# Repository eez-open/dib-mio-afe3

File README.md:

### Ownership and License
The contributors are listed in CONTRIB.TXT.

Licenses | OSHWA UID
--|--
 | 

### Overview

The [EEZ DIB](https://github.com/eez-open/modular-psu) 4-channel Hi-voltage/Hi-current AFE for [MIO168](https://github.com/eez-open/dib-mio168) module with two isolated inputs for voltage and current measurements.

### Feature list
* [ADS131E04](https://www.ti.com/product/ADS131E04) 24-bit 4-channel simultaneous sampling ADC with SPI
* AIN#1: Hi-voltage isolated (floated) input featuring 2 measurement ranges (±50 V, ±450 V)
* AIN#2: Hi-current isolated (floated) input featuring 2 measurement ranges (±1 A, ±10 A)
* AIN#3: Hi-voltage input featuring 3 measurement ranges (±2.4 V, ±48 V, ±240 V)
* AIN#4: Hi-current input featuring 3 measurement ranges (±24 mA, ±1.2 A, ±10 A), share common GND with AIN#3
* Latching relays for lower continuous power consumption
* Fused current inputs
* On-board ±2.5 V low noise LDOs
* Optional external voltage reference
* Dimensions: 132 x 68.5 mm, 4-layer PCB

### r1B4 prototype 3D model

### KiCad project (v7 or newer)

* [AFE3 r1B4](https://github.com/eez-open/dib-mio-afe3/tree/master/EDA%20files/KiCad)

All symbols, footprints and 3D models used in the project can be found in the [EEZ-DIB Library](https://github.com/eez-open/eez-kicad-libraries) plugin for KiCad.

### Bill of materials

* [Download](https://github.com/eez-open/dib-mio-afe3/tree/master/EDA%20files/KiCad/bom/ibom.html) as raw file _Interactive BOM_ (ibom.html) and open it locally in your browser.

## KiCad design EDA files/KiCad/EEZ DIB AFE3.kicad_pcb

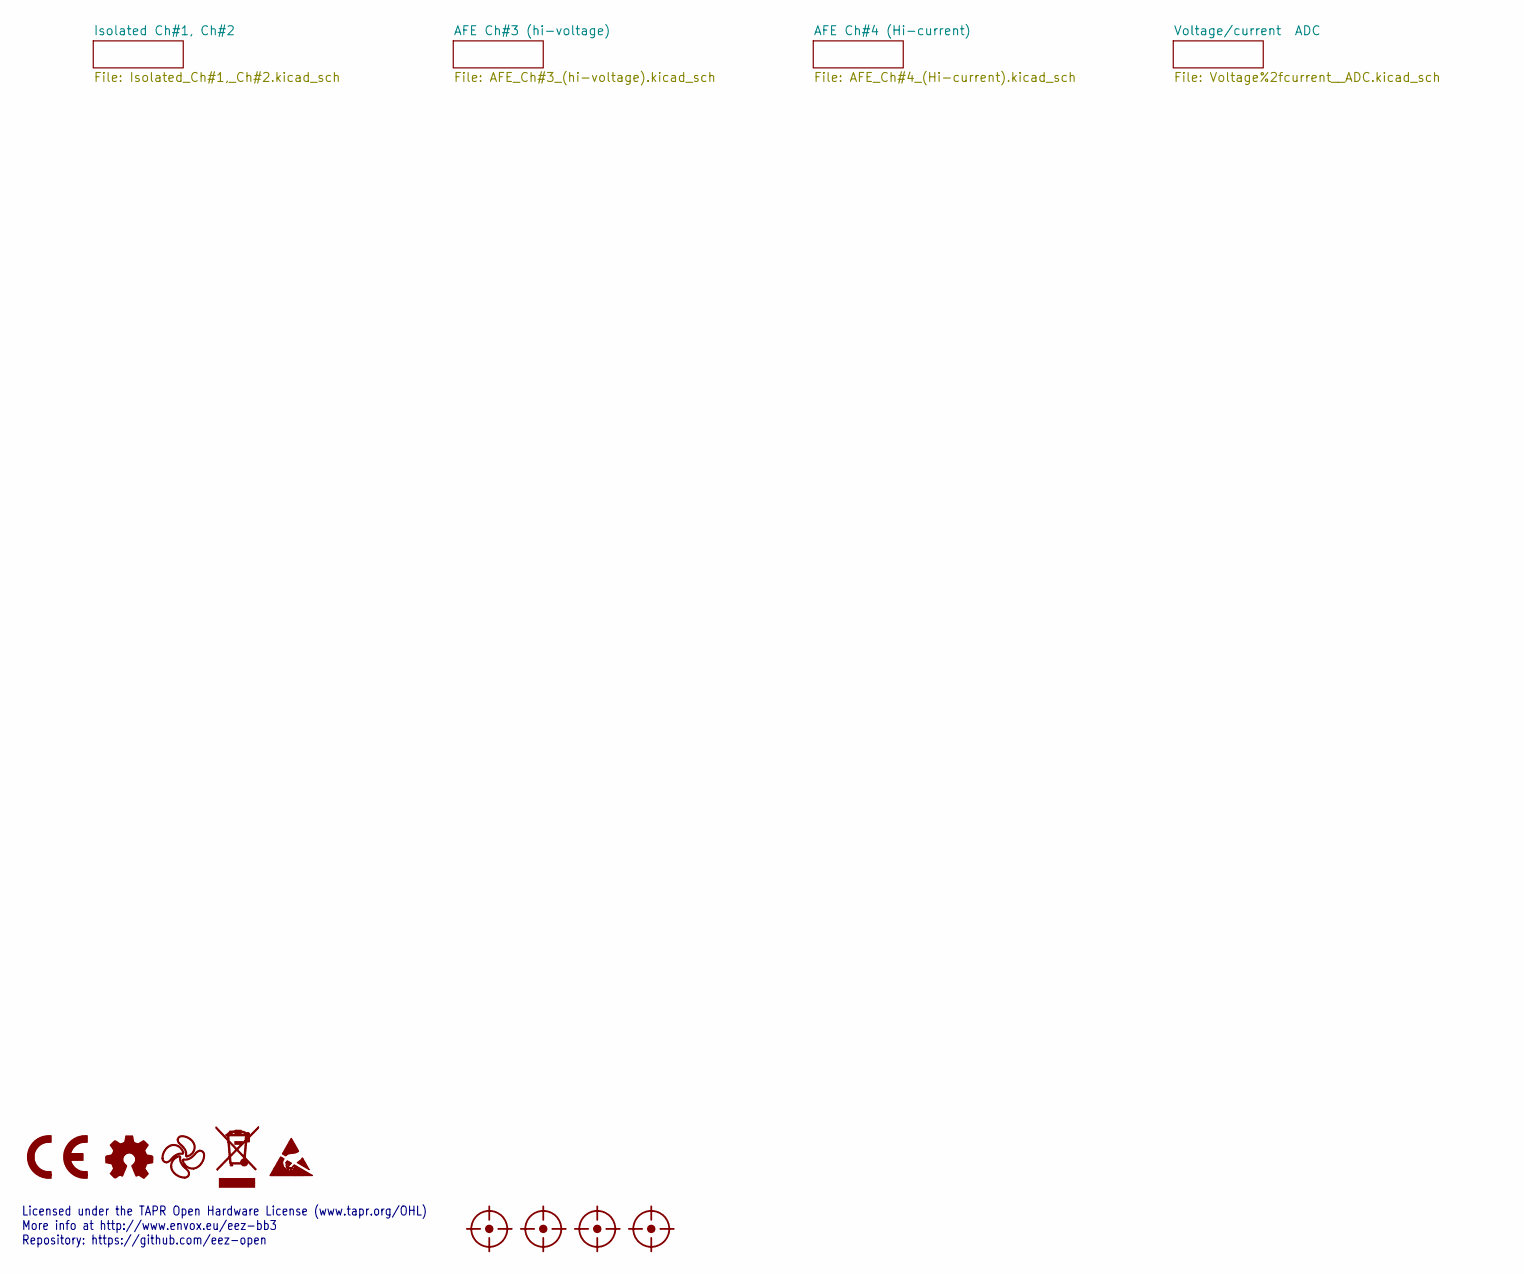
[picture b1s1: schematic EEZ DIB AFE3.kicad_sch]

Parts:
FM1, FM2, FM3, FM4: FIDUCIAL_2; Fiducial
LOGO1: CR logo; CE logo
LOGO2: Open HW logo
LOGO3: EEZ logo; EEZ logo (outline 6mm)
LOGO4: WEEE logo
LOGO5: ESD logo

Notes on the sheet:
Licensed under the TAPR Open Hardware License (www.tapr.org/OHL) More info at http://www.envox.eu/eez-bb3 Repository: https://github.com/eez-open

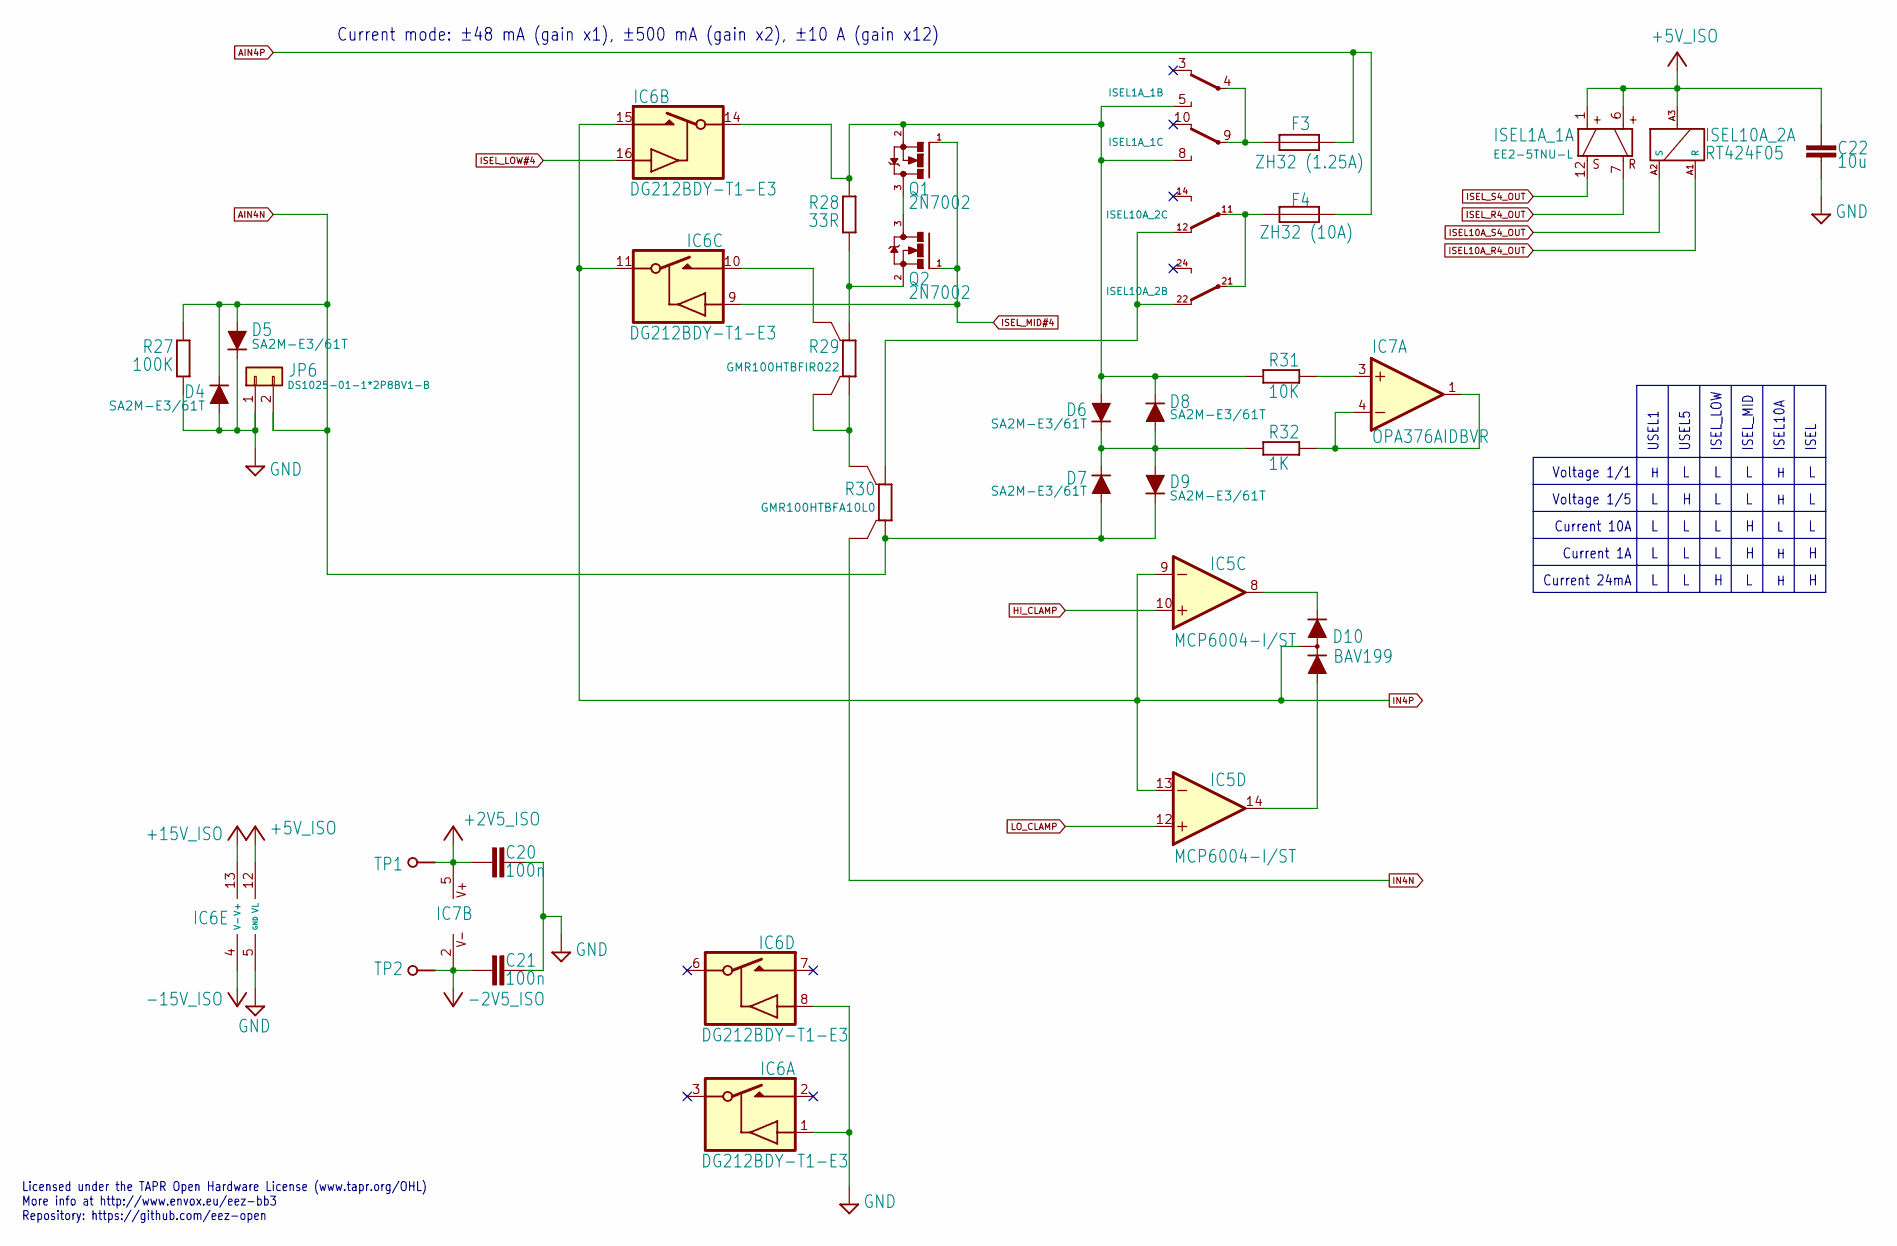
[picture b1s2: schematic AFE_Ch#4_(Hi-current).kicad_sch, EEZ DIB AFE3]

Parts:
C20, C21: 100n; C_0603_1608Metric; DigiKey 490-4774-1-ND
C22: 10u; C_1206_3216Metric; DigiKey 1276-2872-1-ND
D4, D5, D6, D7, D8, D9: SA2M-E3/61T; DO214AC-2; DigiKey CSA2M-E3/IGICT-ND
D10: BAV199; SOT23-3; DigiKey 1727-6382-1-ND
F3: ZH32 (1.25A); ZH32; DigiKey 732-11370-ND
F4: ZH32 (10A); ZH32; DigiKey 732-11370-ND
IC5: MCP6004-I/ST; PW(R-PDSO-G14); DigiKey MCP6004T-I/STTR-ND
IC6: DG212BDY-T1-E3; SO16; DigiKey DG212BDY-T1-E3CT-ND
IC7: OPA376AIDBVR; SOT23-5L_STM; DigiKey 296-39130-2-ND
ISEL1A_1: EE2-5TNU-L; DigiKey 399-11021-1-ND
ISEL10A_2: RT424F05; DigiKey PB2024-ND
JP6: DS1025-01-1*2P8BV1-B; 2MM-2; DigiKey 2057-2PH1-02-UA-ND
Q1, Q2: 2N7002; SOT103P240X110-3N; DigiKey 2N7002LT1GOSCT-ND
R27: 100K; R_1206_3216Metric; DigiKey RMCF0805FT100KCT-ND
R28: 33R; R_1206_3216Metric; DigiKey 13-RT1206BRD0733RLCT-ND
R29: GMR100HTBFIR022; R_2512-4WIRE; DigiKey 511-1688-1-ND
R30: GMR100HTBFA10L0; R_2512-4WIRE; DigiKey 511-1686-1-ND
R31: 10K; R_0805_2012Metric; DigiKey 311-10.0KCRCT-ND
R32: 1K; R_0805_2012Metric; DigiKey RC0805FR-071KL
TP1, TP2: PCB_TEST_TABSHIELD; Testhole 24_50mils

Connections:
+2V5_ISO: C20.2, IC7.5 (V+), TP1.1; also elsewhere on the board
+5V_ISO: C22.1, IC6.12 (VL), ISEL1A_1.1 (S+), ISEL1A_1.6 (R+), ISEL10A_2.A3; also elsewhere on the board
+15V_ISO: IC6.13 (V+); also elsewhere on the board
-2V5_ISO: C21.2, IC7.2 (V-), TP2.1; also elsewhere on the board
-15V_ISO: IC6.4 (V-); also elsewhere on the board
AIN4N: D4.C, D5.A, D7.A, D9.C, JP6.2, R27.2, R30.1; also elsewhere on the board
AIN4P: F3.2, F4.2; also elsewhere on the board
GND: C20.1, C21.1, C22.2, D4.A, D5.C, IC6.1 (IN), IC6.5 (GND), IC6.8 (IN), JP6.1, R27.1; also elsewhere on the board
HI_CLAMP: IC5.10 (+IN); also elsewhere on the board
IN4N: R30.1S; also elsewhere on the board
IN4P: D10.3 (AC), IC5.9 (-IN), IC5.13 (-IN), IC6.11 (S), IC6.15 (D); also elsewhere on the board
ISEL10A_R4_OUT: ISEL10A_2.A1 (R); also elsewhere on the board
ISEL10A_S4_OUT: ISEL10A_2.A2 (S); also elsewhere on the board
ISEL_LOW#4: IC6.16 (IN); also elsewhere on the board
ISEL_MID#4: IC6.9 (IN), Q1.1 (G), Q2.1 (G); also elsewhere on the board
ISEL_R4_OUT: ISEL1A_1.7 (R-); also elsewhere on the board
ISEL_S4_OUT: ISEL1A_1.12 (S-); also elsewhere on the board
LO_CLAMP: IC5.12 (+IN); also elsewhere on the board
unnamed: D6.C, D7.C, D8.A, D9.A, R32.2
unnamed: D10.1 (A), IC5.14 (OUT)
unnamed: D10.2 (C), IC5.8 (OUT)
unnamed: F4.1, ISEL10A_2.11, ISEL10A_2.21
unnamed: D6.A, D8.C, IC6.14 (S), ISEL1A_1.5 (NO), ISEL1A_1.8 (NO), Q1.2 (S), R28.2, R31.2
unnamed: IC6.10 (D), R29.2S
unnamed: IC7.3 (+IN), R31.1
unnamed: IC7.1 (OUT), IC7.4 (-IN), R32.1
unnamed: F3.1, ISEL1A_1.4 (COM), ISEL1A_1.9 (COM)
unnamed: ISEL10A_2.12, ISEL10A_2.22, R30.2
unnamed: Q1.3 (D), Q2.3 (D)
unnamed: Q2.2 (S), R28.1, R29.2
unnamed: R29.1, R29.1S, R30.2S

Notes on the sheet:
Current 24mA
Voltage 1/1
USEL5
Current 10A
Current mode: ±48 mA (gain x1), ±500 mA (gain x2), ±10 A (gain x12)
ISEL_LOW
ISEL
USEL1
ISEL_MID
Current 1A
Voltage 1/5
Licensed under the TAPR Open Hardware License (www.tapr.org/OHL) More info at http://www.envox.eu/eez-bb3 Repository: https://github.com/eez-open
ISEL10A

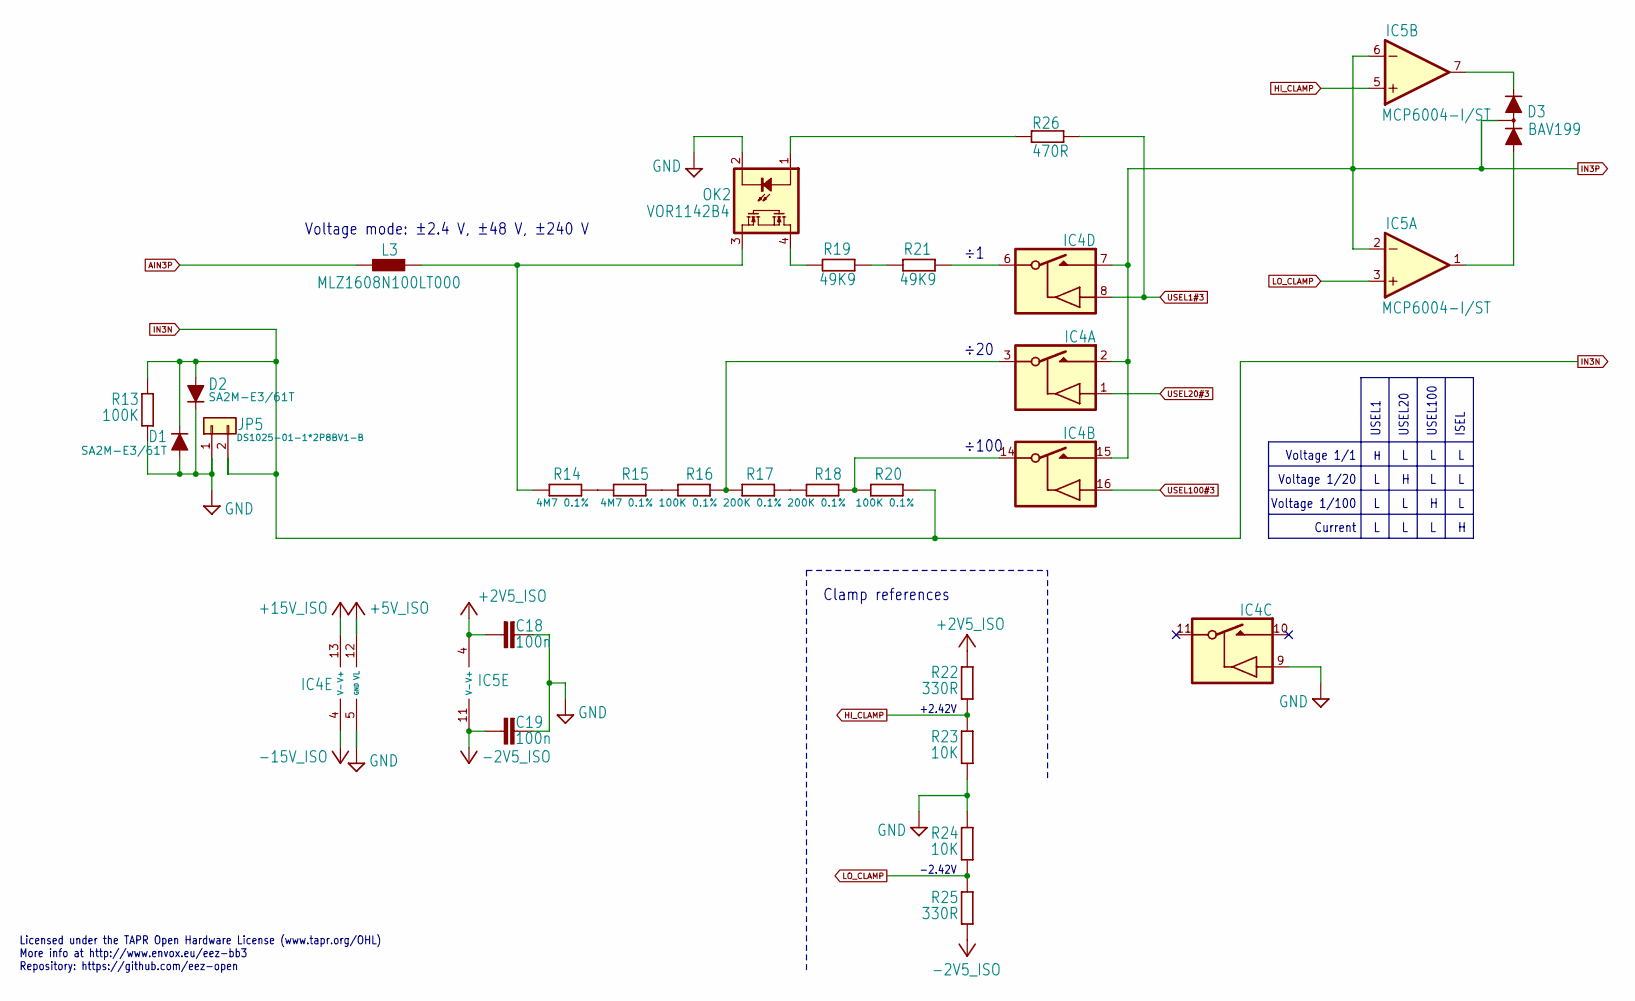
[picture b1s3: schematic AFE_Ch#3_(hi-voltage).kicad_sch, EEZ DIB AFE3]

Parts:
C18, C19: 100n; C_0603_1608Metric; DigiKey 490-4774-1-ND
D1, D2: SA2M-E3/61T; DO214AC-2; DigiKey CSA2M-E3/IGICT-ND
D3: BAV199; SOT23-3; DigiKey 1727-6382-1-ND
IC4: DG212BDY-T1-E3; SO16; DigiKey DG212BDY-T1-E3CT-ND
IC5: MCP6004-I/ST; PW(R-PDSO-G14); DigiKey MCP6004T-I/STTR-ND
JP5: DS1025-01-1*2P8BV1-B; 2MM-2; DigiKey 2057-2PH1-02-UA-ND
L3: MLZ1608N100LT000; BEAD0603; DigiKey 445-6755-1-ND
OK2: VOR1142B4; DIL4-SMD; DigiKey VOR1142B4-ND
R13: 100K; R_1206_3216Metric; DigiKey RMCF0805FT100KCT-ND
R14, R15: 4M7 0.1%; R_1206_3216Metric; DigiKey 408-2037-1-ND
R16, R20: 100K 0.1%; R_1206_3216Metric; DigiKey RG32P100KBCT-ND
R17, R18: 200K 0.1%; R_1206_3216Metric; DigiKey RG32P200KBCT-ND
R19, R21: 49K9; R_1206_3216Metric; DigiKey RNCP1206FTD49K9CT-ND
R22, R25: 330R; R_0805_2012Metric; DigiKey A106061CT-ND
R23, R24: 10K; R_0805_2012Metric; DigiKey 311-10.0KCRCT-ND
R26: 470R; R_0805_2012Metric; DigiKey 311-470CRCT-ND

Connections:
+2V5_ISO: C18.2, IC5.4 (V+), R22.1; also elsewhere on the board
+5V_ISO: IC4.12 (VL); also elsewhere on the board
+15V_ISO: IC4.13 (V+); also elsewhere on the board
-2V5_ISO: C19.2, IC5.11 (V-), R25.2; also elsewhere on the board
-15V_ISO: IC4.4 (V-); also elsewhere on the board
AIN3P: L3.2; also elsewhere on the board
GND: C18.1, C19.1, D1.A, D2.C, IC4.5 (GND), IC4.9 (IN), JP5.1, OK2.2 (C), R13.1, R23.2, R24.1; also elsewhere on the board
HI_CLAMP: IC5.5 (+IN), R22.2, R23.1; also elsewhere on the board
IN3N: D1.C, D2.A, JP5.2, R13.2, R20.1; also elsewhere on the board
IN3P: D3.3 (AC), IC4.2 (D), IC4.7 (D), IC4.15 (D), IC5.2 (-IN), IC5.6 (-IN); also elsewhere on the board
LO_CLAMP: IC5.3 (+IN), R24.2, R25.1; also elsewhere on the board
unnamed: D3.1 (A), IC5.1 (OUT)
unnamed: D3.2 (C), IC5.7 (OUT)
unnamed: IC4.3 (S), R16.1, R17.2
unnamed: IC4.14 (S), R18.1, R20.2
unnamed: IC4.6 (S), R21.1
unnamed: OK2.1 (A), R26.2
unnamed: OK2.4 (S1), R19.2
unnamed: L3.1, OK2.3 (S2), R14.2
unnamed: R14.1, R15.2
unnamed: R15.1, R16.2
unnamed: R17.1, R18.2
unnamed: R19.1, R21.2
USEL1#3: IC4.8 (IN), R26.1; also elsewhere on the board
USEL20#3: IC4.1 (IN); also elsewhere on the board
USEL100#3: IC4.16 (IN); also elsewhere on the board

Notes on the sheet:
-2.42V
Current
USEL100
ISEL
Licensed under the TAPR Open Hardware License (www.tapr.org/OHL) More info at http://www.envox.eu/eez-bb3 Repository: https://github.com/eez-open
÷100
USEL20
+2.42V
Voltage 1/1
Voltage mode: ±2.4 V, ±48 V, ±240 V
Voltage 1/100
Clamp references
Voltage 1/20
USEL1
÷20

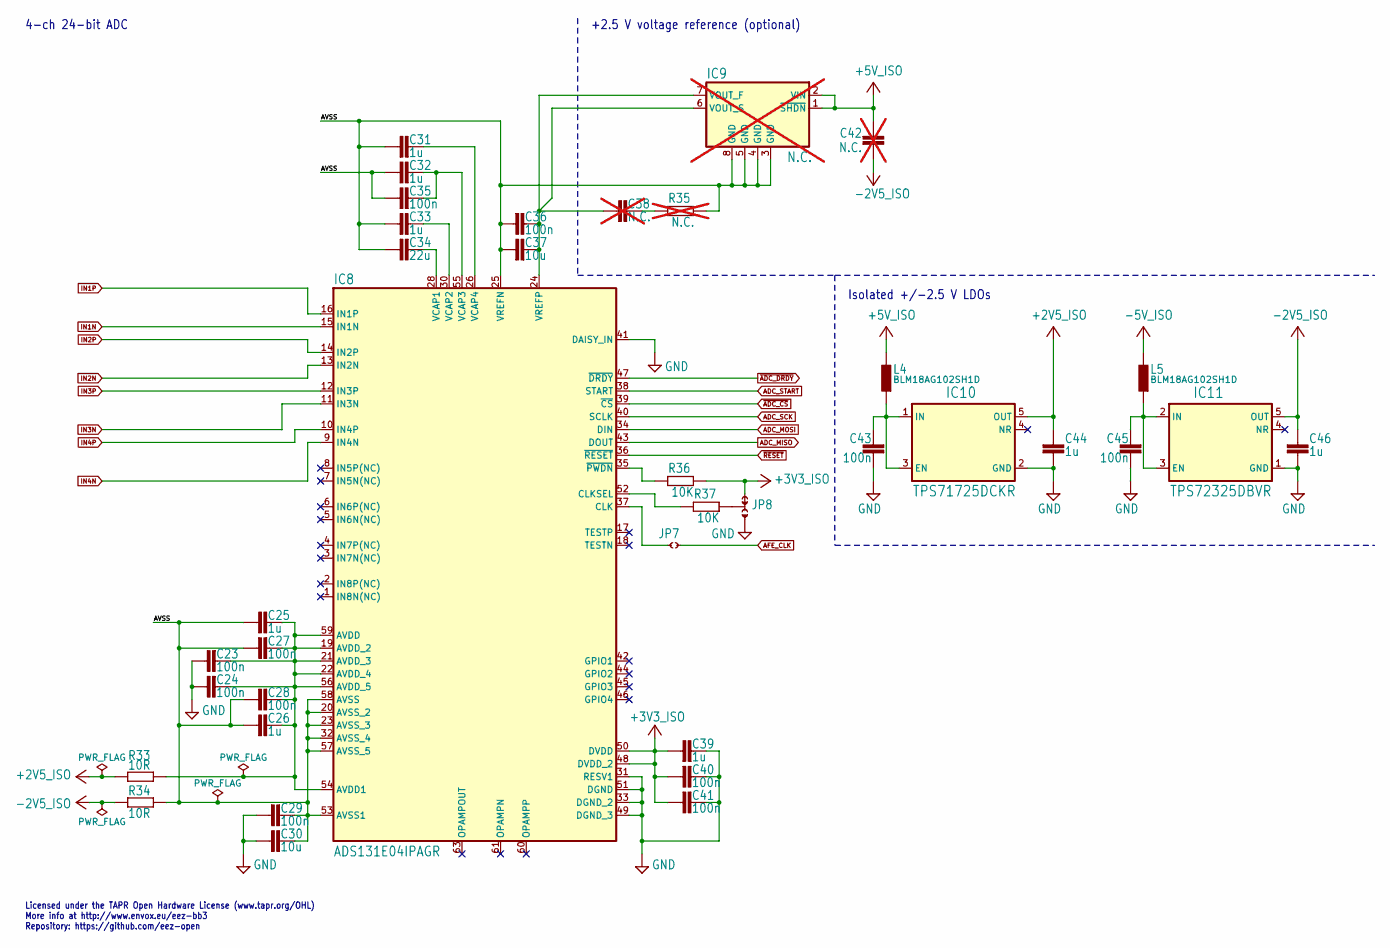
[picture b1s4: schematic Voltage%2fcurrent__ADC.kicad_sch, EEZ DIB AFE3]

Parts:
C23, C24, C27, C28, C29, C35, C36, C40, C41, C43, C45: 100n; C_0603_1608Metric; DigiKey 490-4774-1-ND
C25, C26, C31, C32, C33, C39, C44, C46: 1u; C_0603_1608Metric; DigiKey 1276-1019-1-ND
C30, C37: 10u; C_1206_3216Metric; DigiKey 1276-2872-1-ND
C34: 22u; C_1206_3216Metric; DigiKey 1276-3373-1-ND
C38, C42: N.C.; C_1206_3216Metric; not fitted
IC8: ADS131E04IPAGR; PAG64; DigiKey 296-34885-1-ND
IC9: N.C.; MSOP-8_MS_LIT; DigiKey 505-LTC6655BHMS8-2.5#TRPBFTR-ND; not fitted
IC10: TPS71725DCKR; DCK5; DigiKey 296-21525-1-ND
IC11: TPS72325DBVR; DBV5; DigiKey 296-39479-1-ND
JP7: JP2-CUT-0805; JP2 open
JP8: JP3-CUT-0805-ROTATED; JP3 shorted
L4, L5: BLM18AG102SH1D; BEAD0603; DigiKey 490-7809-1-ND
R33, R34: 10R; R_0805_2012Metric; DigiKey 2019-RK73H2ATTD10R0FCT-ND
R35: N.C.; R_0805_2012Metric; not fitted
R36, R37: 10K; R_0805_2012Metric; DigiKey 311-10.0KCRCT-ND

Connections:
+2V5_ISO: C44.2, IC10.5 (OUT), R33.1; also elsewhere on the board
+3V3_ISO: C39.1, C40.2, C41.2, IC8.48 (DVDD_2), IC8.50 (DVDD), JP8.NC, R36.2; also elsewhere on the board
+5V_ISO: C42.1, IC9.1 (~SHDN), IC9.2 (VIN), L4.2; also elsewhere on the board
-2V5_ISO: C42.2, C46.2, IC11.5 (OUT), R34.2; also elsewhere on the board
-5V_ISO: L5.2; also elsewhere on the board
/Voltage/current ADC/AVSS: C25.1, C26.1, C27.2, C28.2, C29.1, C30.1, C31.1, C32.1, C33.1, C34.1, C35.2, C36.2, C37.2, IC8.20 (AVSS_2), IC8.23 (AVSS_3), IC8.25 (VREFN), IC8.32 (AVSS_4), IC8.53 (AVSS1), IC8.57 (AVSS_5), IC8.58 (AVSS), IC9.3 (GND), IC9.4 (GND), IC9.5 (GND), IC9.8 (GND), R34.1, R35.2
ADC_MISO: IC8.43 (DOUT); also elsewhere on the board
ADC_MOSI: IC8.34 (DIN); also elsewhere on the board
ADC_SCK: IC8.40 (SCLK); also elsewhere on the board
ADC_START: IC8.38 (START); also elsewhere on the board
AFE_CLK: JP7.1; also elsewhere on the board
GND: C23.2, C24.2, C29.2, C30.2, C39.2, C40.1, C41.1, C43.2, C44.1, C45.2, C46.1, IC8.31 (RESV1), IC8.33 (DGND_2), IC8.41 (DAISY_IN), IC8.49 (DGND_3), IC8.51 (DGND), IC10.2 (GND), IC11.1 (GND), JP8.NO; also elsewhere on the board
IN1N: IC8.15 (IN1N); also elsewhere on the board
IN1P: IC8.16 (IN1P); also elsewhere on the board
IN2N: IC8.13 (IN2N); also elsewhere on the board
IN2P: IC8.14 (IN2P); also elsewhere on the board
IN3N: IC8.11 (IN3N); also elsewhere on the board
IN3P: IC8.12 (IN3P); also elsewhere on the board
IN4N: IC8.9 (IN4N); also elsewhere on the board
IN4P: IC8.10 (IN4P); also elsewhere on the board
unnamed: C38.2, R35.1
unnamed: C23.1, C24.1, C25.2, C26.2, C27.1, C28.1, IC8.19 (AVDD_2), IC8.21 (AVDD_3), IC8.22 (AVDD_4), IC8.54 (AVDD1), IC8.56 (AVDD_5), IC8.59 (AVDD), R33.2
unnamed: IC8.37 (CLK), JP7.2
unnamed: IC8.52 (CLKSEL), R37.1
unnamed: C34.2, IC8.28 (VCAP1)
unnamed: C33.2, IC8.30 (VCAP2)
unnamed: C32.2, C35.1, IC8.55 (VCAP3)
unnamed: C31.2, IC8.26 (VCAP4)
unnamed: C36.1, C37.1, C38.1, IC8.24 (VREFP), IC9.6 (VOUT_S), IC9.7 (VOUT_F)
unnamed: IC8.35 (~PWDN), R36.1
unnamed: C43.1, IC10.1 (IN), IC10.3 (EN), L4.1
unnamed: C45.1, IC11.2 (IN), IC11.3 (EN), L5.1
unnamed: JP8.COM, R37.2
~ADC_CS: IC8.39 (~CS); also elsewhere on the board
~ADC_DRDY: IC8.47 (~DRDY); also elsewhere on the board
~RESET: IC8.36 (~RESET); also elsewhere on the board

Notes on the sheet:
4-ch 24-bit ADC
Isolated +/-2.5 V LDOs
+2.5 V voltage reference (optional)
Licensed under the TAPR Open Hardware License (www.tapr.org/OHL) More info at http://www.envox.eu/eez-bb3 Repository: https://github.com/eez-open

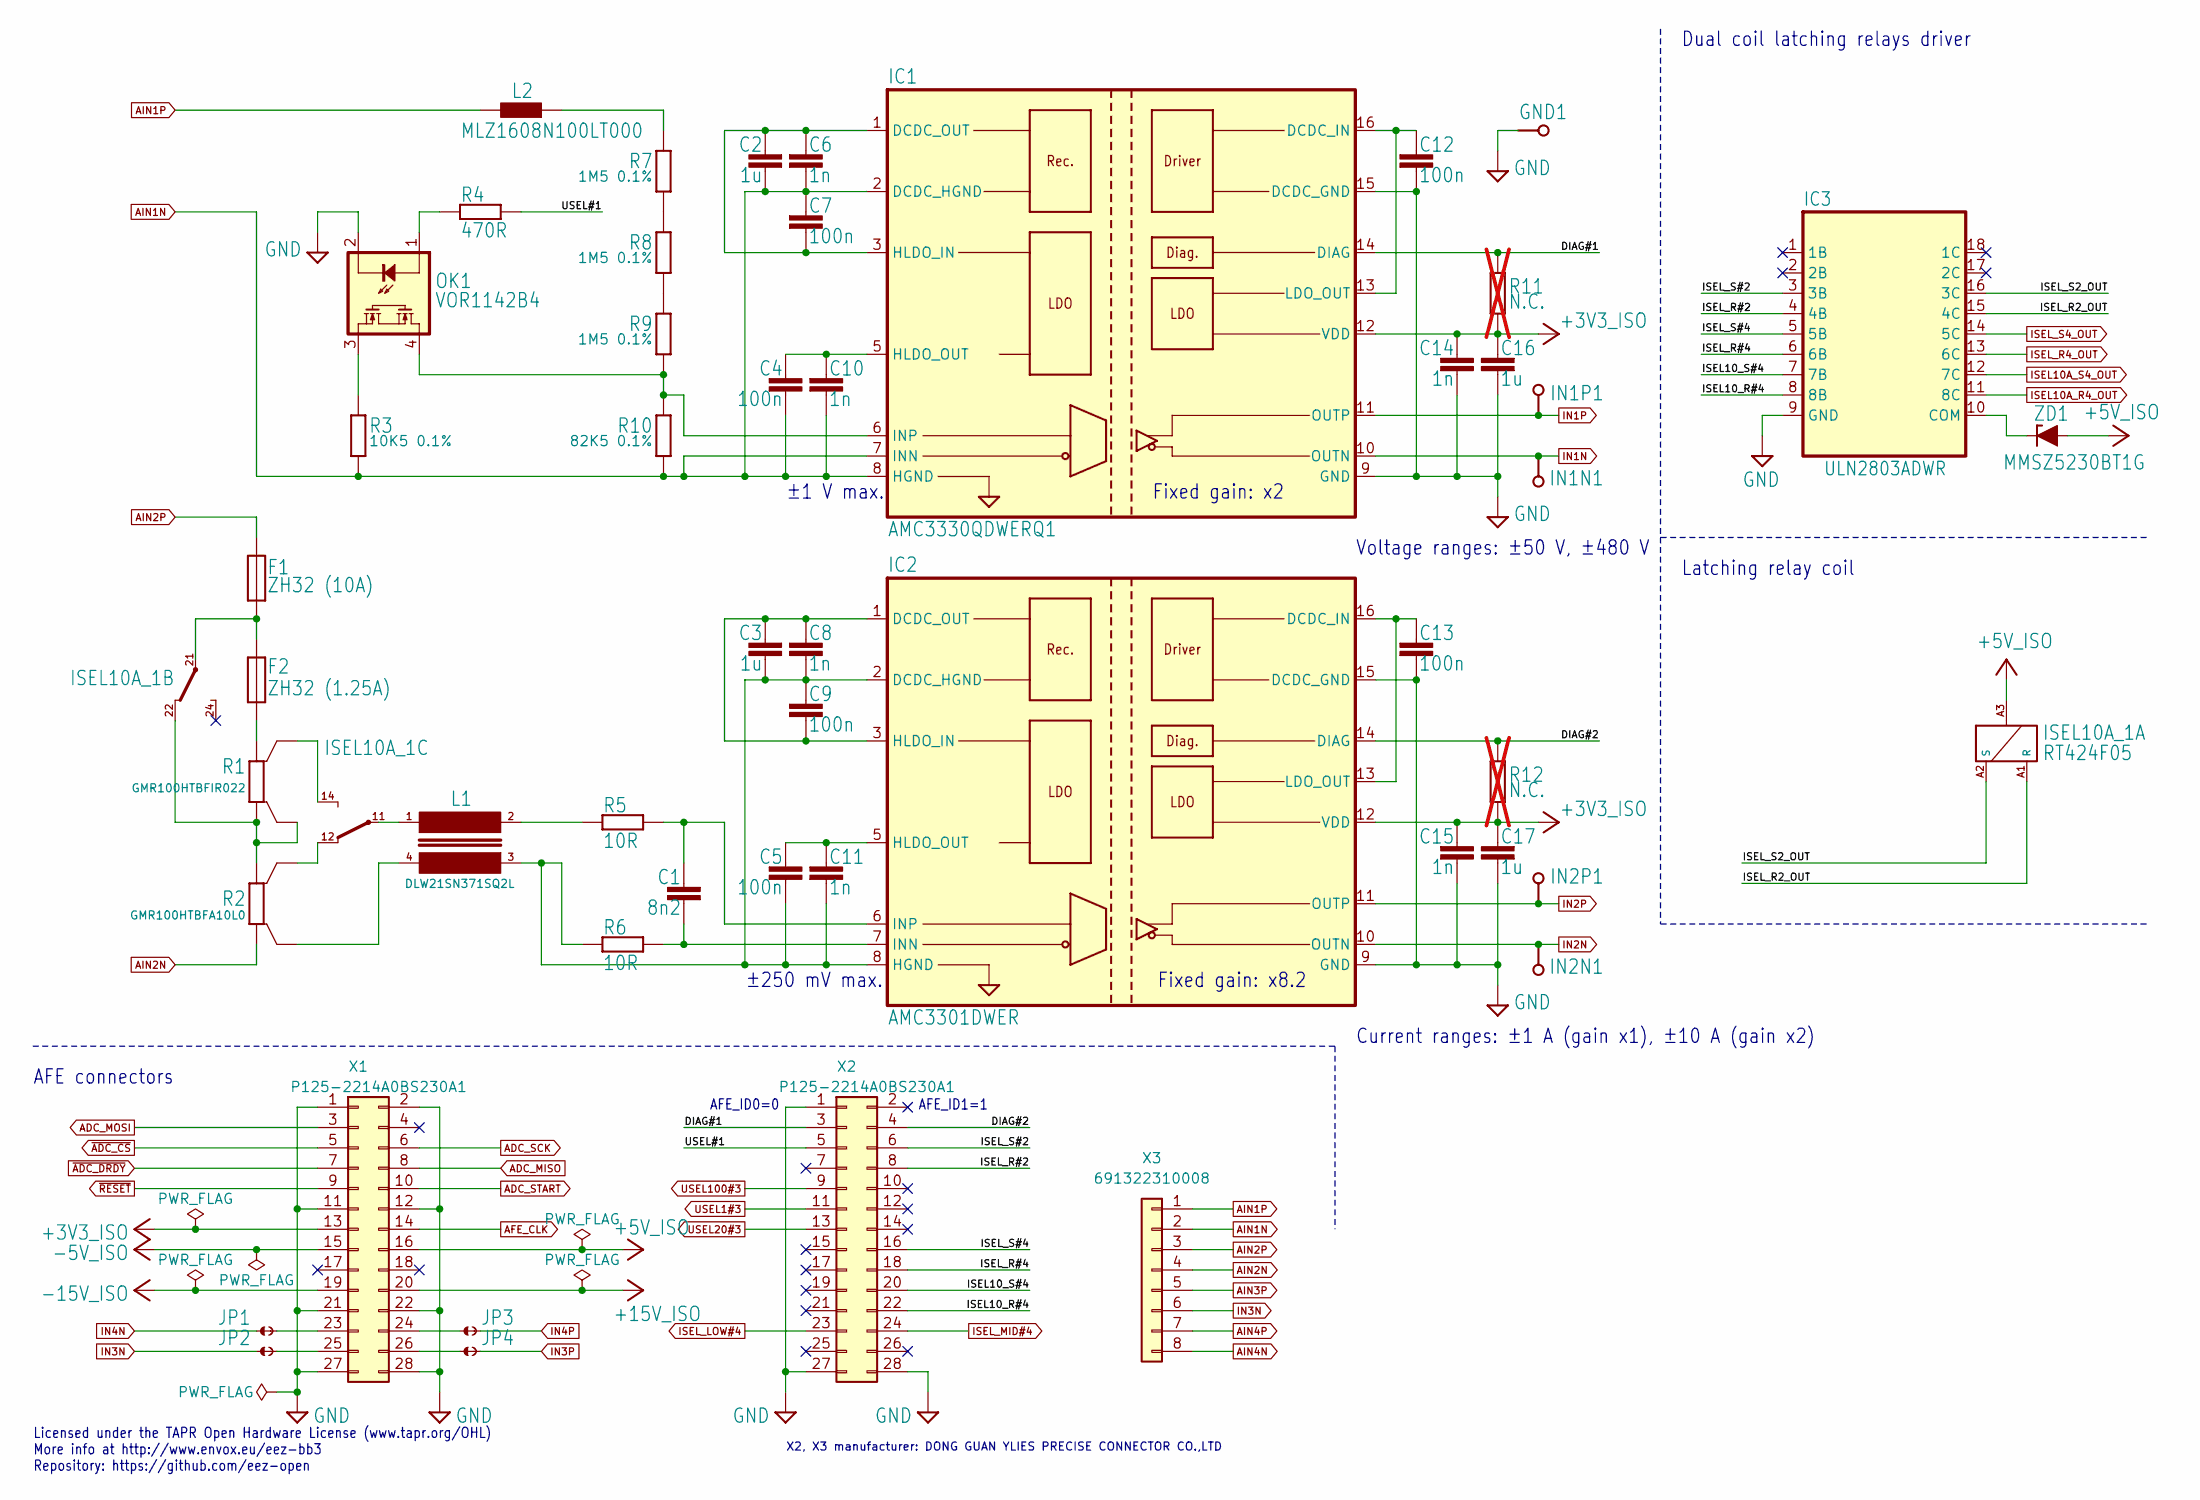
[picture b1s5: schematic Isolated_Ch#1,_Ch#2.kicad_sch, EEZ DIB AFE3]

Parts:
C1: 8n2; C_0603_1608Metric; DigiKey 311-1811-1-ND
C2, C3: 1u; C_0603_1608Metric; DigiKey 1276-1019-1-ND
C4, C5: 100n; C_1206_3216Metric; DigiKey 399-C1206C104K5RAC7800CT-ND
C6, C8: 1n; C_0603_1608Metric; DigiKey 1276-1018-1-ND
C7, C9, C12, C13: 100n; C_0603_1608Metric; DigiKey 490-4774-1-ND
C10, C11, C14, C15: 1n; C_1206_3216Metric; DigiKey 732-8115-1-ND
C16, C17: 1u; C_1206_3216Metric; DigiKey 1276-3091-1-ND
F1: ZH32 (10A); ZH32; DigiKey 732-11370-ND
F2: ZH32 (1.25A); ZH32; DigiKey 732-11370-ND
GND1: PCB_TEST_TABSHIELD; Testhole 24_50mils
IC1: AMC3330QDWERQ1; DW16; DigiKey 296-AMC3330DWERCT-ND
IC2: AMC3301DWER; DW16; DigiKey 296-AMC3301QDWERQ1CT-ND
IC3: ULN2803ADWR; DW18_TEX-M; DigiKey 296-15777-1-ND
IN1N1, IN1P1, IN2N1, IN2P1: PCB_TEST_TABSHIELD; Testhole 24_50mils
ISEL10A_1: RT424F05; DigiKey PB2024-ND
JP1, JP2, JP3, JP4: JP2-NOCUT-0805; JP2 shorted
L1: DLW21SN371SQ2L; IND_DLW21S_0805_MUR-M; DigiKey 490-5141-1-ND
L2: MLZ1608N100LT000; BEAD0603; DigiKey 445-6755-1-ND
OK1: VOR1142B4; DIL4-SMD; DigiKey VOR1142B4-ND
R1: GMR100HTBFIR022; R_2512-4WIRE; DigiKey 511-1688-1-ND
R2: GMR100HTBFA10L0; R_2512-4WIRE; DigiKey 511-1686-1-ND
R3: 10K5 0.1%; R_1206_3216Metric; DigiKey A140954CT-ND
R4: 470R; R_0805_2012Metric; DigiKey 311-470CRCT-ND
R5, R6: 10R; R_0805_2012Metric; DigiKey 2019-RK73H2ATTD10R0FCT-ND
R7, R8, R9: 1M5 0.1%; R_1206_3216Metric; DigiKey RG3216P-1504-B-T1
R10: 82K5 0.1%; R_1206_3216Metric; DigiKey RQ73C2B82K5BTD
R11, R12: N.C.; R_0805_2012Metric; not fitted
X1, X2: P125-2214A0BS230A1
X3: 691322310008; DigiKey 732-2093-ND
ZD1: MMSZ5230BT1G; SOD123; DigiKey MMSZ5230BT1GOSCT-ND

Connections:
+3V3_ISO: C14.1, C15.1, C16.1, C17.1, IC1.12 (VDD), IC2.12 (VDD), R11.2, R12.2, X1.13; also elsewhere on the board
+5V_ISO: ISEL10A_1.A3, X1.16, ZD1.A; also elsewhere on the board
+15V_ISO: X1.20; also elsewhere on the board
-5V_ISO: X1.15; also elsewhere on the board
-15V_ISO: X1.19; also elsewhere on the board
/Isolated Ch#1, Ch#2/DIAG#1: IC1.14 (DIAG), R11.1, X2.3
/Isolated Ch#1, Ch#2/DIAG#2: IC2.14 (DIAG), R12.1, X2.4
/Isolated Ch#1, Ch#2/ISEL10_R#4: IC3.8 (8B), X2.22
/Isolated Ch#1, Ch#2/ISEL10_S#4: IC3.7 (7B), X2.20
/Isolated Ch#1, Ch#2/ISEL_R2_OUT: IC3.15 (4C), ISEL10A_1.A1 (R)
/Isolated Ch#1, Ch#2/ISEL_R#2: IC3.4 (4B), X2.8
/Isolated Ch#1, Ch#2/ISEL_R#4: IC3.6 (6B), X2.18
/Isolated Ch#1, Ch#2/ISEL_S2_OUT: IC3.16 (3C), ISEL10A_1.A2 (S)
/Isolated Ch#1, Ch#2/ISEL_S#2: IC3.3 (3B), X2.6
/Isolated Ch#1, Ch#2/ISEL_S#4: IC3.5 (5B), X2.16
/Isolated Ch#1, Ch#2/USEL#1: R4.2, X2.5
ADC_MISO: X1.8; also elsewhere on the board
ADC_MOSI: X1.3; also elsewhere on the board
ADC_SCK: X1.6; also elsewhere on the board
ADC_START: X1.10; also elsewhere on the board
AFE_CLK: X1.14; also elsewhere on the board
AIN1N: C2.2, C4.2, C6.2, C7.1, C10.2, IC1.2 (DCDC_HGND), IC1.7 (INN), IC1.8 (HGND), R3.1, R10.1, X3.2; also elsewhere on the board
AIN1P: L2.2, X3.1; also elsewhere on the board
AIN2N: R2.1, X3.4; also elsewhere on the board
AIN2P: F1.2, X3.3; also elsewhere on the board
GND: C12.2, C13.2, C14.2, C15.2, C16.2, C17.2, GND1.1, IC1.9 (GND), IC1.15 (DCDC_GND), IC2.9 (GND), IC2.15 (DCDC_GND), IC3.9 (GND), OK1.2 (C), X1.1, X1.2, X1.11, X1.12, X1.21, X1.22, X1.27, X1.28, X2.1, X2.27, X2.28; also elsewhere on the board
IN1N: IC1.10 (OUTN), IN1N1.1; also elsewhere on the board
IN1P: IC1.11 (OUTP), IN1P1.1; also elsewhere on the board
IN2N: IC2.10 (OUTN), IN2N1.1; also elsewhere on the board
IN2P: IC2.11 (OUTP), IN2P1.1; also elsewhere on the board
IN3N: JP2.1, X3.6; also elsewhere on the board
IN3P: JP4.2; also elsewhere on the board
IN4N: JP1.1; also elsewhere on the board
IN4P: JP3.2; also elsewhere on the board
ISEL10A_R4_OUT: IC3.11 (8C); also elsewhere on the board
ISEL10A_S4_OUT: IC3.12 (7C); also elsewhere on the board
ISEL_LOW#4: X2.23; also elsewhere on the board
ISEL_MID#4: X2.24; also elsewhere on the board
ISEL_R4_OUT: IC3.13 (6C); also elsewhere on the board
ISEL_S4_OUT: IC3.14 (5C); also elsewhere on the board
unnamed: F1.1, F2.1, ISEL10A_1.21
unnamed: F2.2, R1.2
unnamed: C12.1, IC1.13 (LDO_OUT), IC1.16 (DCDC_IN)
unnamed: C2.1, C6.1, C7.2, IC1.1 (DCDC_OUT), IC1.3 (HLDO_IN)
unnamed: C4.1, C10.1, IC1.5 (HLDO_OUT)
unnamed: IC1.6 (INP), OK1.4 (S1), R9.1, R10.2
unnamed: C3.2, C5.2, C8.2, C9.1, C11.2, IC2.2 (DCDC_HGND), IC2.8 (HGND), L1.3, R6.2
unnamed: C13.1, IC2.13 (LDO_OUT), IC2.16 (DCDC_IN)
unnamed: C3.1, C8.1, C9.2, IC2.1 (DCDC_OUT), IC2.3 (HLDO_IN)
unnamed: C5.1, C11.1, IC2.5 (HLDO_OUT)
unnamed: C1.2, IC2.7 (INN), R6.1
unnamed: C1.1, IC2.6 (INP), R5.1
unnamed: IC3.10 (COM), ZD1.C
unnamed: ISEL10A_1.11, L1.1
unnamed: ISEL10A_1.12, R2.2S
unnamed: ISEL10A_1.14, R1.2S
unnamed: ISEL10A_1.22, R1.1, R1.1S, R2.2
unnamed: L1.2, R5.2
unnamed: L1.4, R2.1S
unnamed: L2.1, R7.2
unnamed: OK1.1 (A), R4.1
unnamed: OK1.3 (S2), R3.2
unnamed: R7.1, R8.2
unnamed: R8.1, R9.2
unnamed: JP1.2, X1.23
unnamed: JP3.1, X1.24
unnamed: JP2.2, X1.25
unnamed: JP4.1, X1.26
USEL1#3: X2.11; also elsewhere on the board
USEL20#3: X2.13; also elsewhere on the board
USEL100#3: X2.9; also elsewhere on the board
~ADC_CS: X1.5; also elsewhere on the board
~ADC_DRDY: X1.7; also elsewhere on the board
~RESET: X1.9; also elsewhere on the board

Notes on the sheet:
Current ranges: ±1 A (gain x1), ±10 A (gain x2)
AFE_ID1=1
Licensed under the TAPR Open Hardware License (www.tapr.org/OHL) More info at http://www.envox.eu/eez-bb3 Repository: https://github.com/eez-open
±250 mV max.
Fixed gain: x2
AFE connectors
Voltage ranges: ±50 V, ±480 V
Dual coil latching relays driver
±1 V max.
Latching relay coil
AFE_ID0=0
Fixed gain: x8.2
X2, X3 manufacturer: DONG GUAN YLIES PRECISE CONNECTOR CO.,LTD

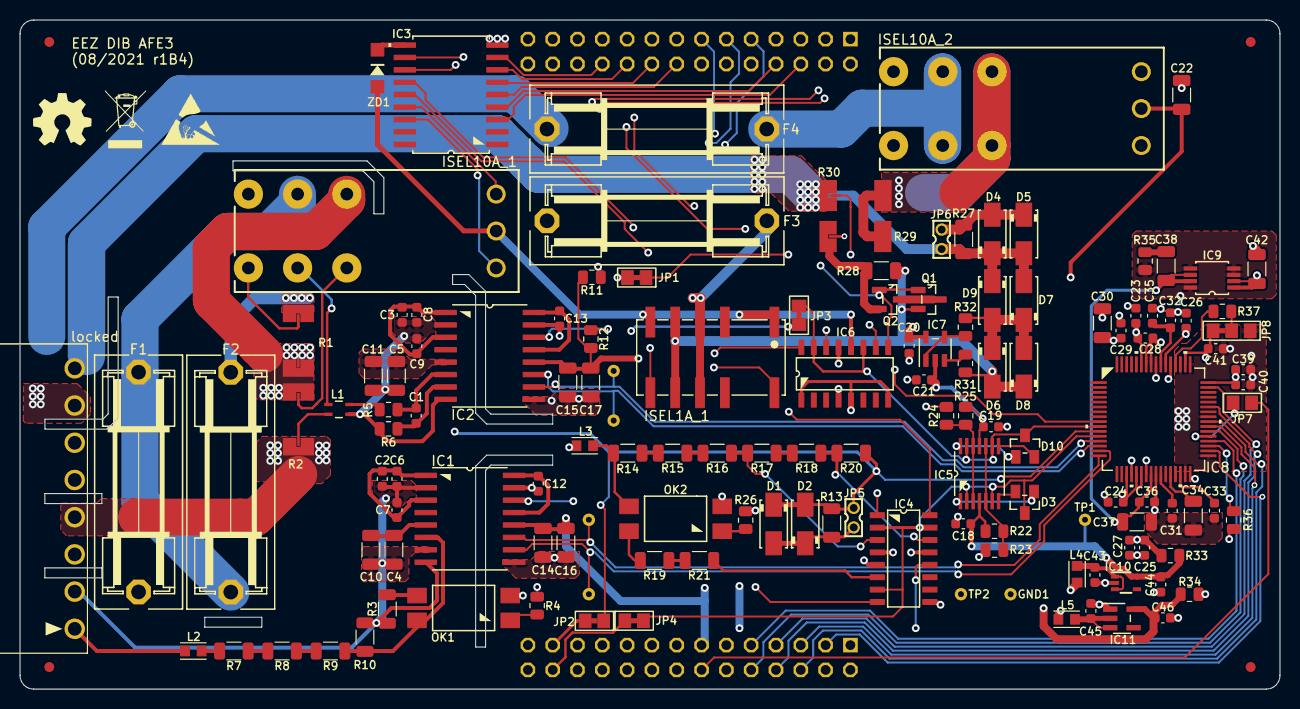
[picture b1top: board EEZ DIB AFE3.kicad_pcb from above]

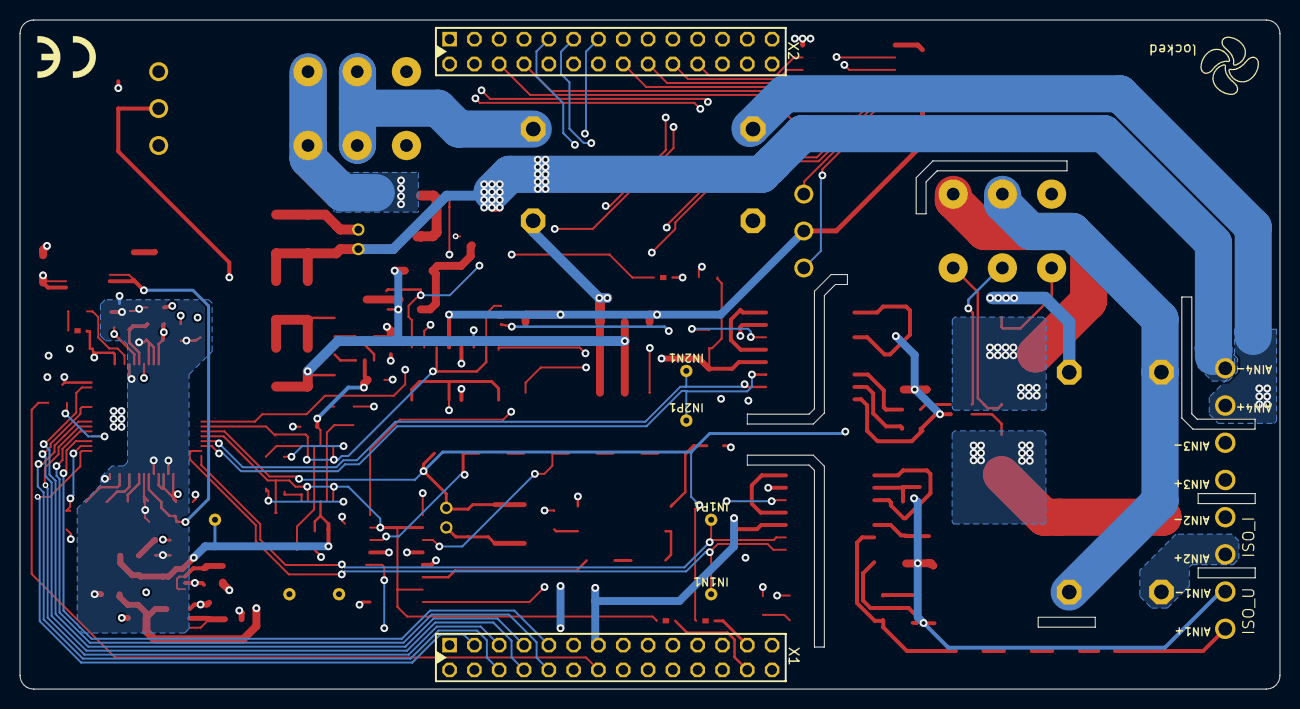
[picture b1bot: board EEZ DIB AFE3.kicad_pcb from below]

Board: 4 copper layers, 129.0 x 68.5 mm, 148 parts (8 on the bottom side), 120 nets.

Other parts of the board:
locked: 691322310008

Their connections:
AIN1N: locked.2; also elsewhere on the board
AIN1P: locked.1; also elsewhere on the board
AIN2N: locked.4; also elsewhere on the board
AIN2P: locked.3; also elsewhere on the board
AIN3P: locked.5; also elsewhere on the board
AIN4N: locked.8; also elsewhere on the board
AIN4P: locked.7; also elsewhere on the board
IN3N: locked.6; also elsewhere on the board

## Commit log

2021-03-31 README.md added
2021-03-31 cleanup
2021-05-07 r1B2 (removed RC from ADC inputs)
2021-05-07 Renaming .sch page files
2021-05-14 New Rsense values, PCB layout adjustment for mid range Rsense
2021-05-14 R30 value corrected
2021-09-29 Gerbers, BOM, schematics update
2021-10-08 OSHWA UID
2024-01-19 #6, #7 (r1B3 KiCad)
2024-01-19 Revert "#6, #7 (r1B3 KiCad)"
    This reverts commit 52033645fb07d7287d4da63e50f45c25d80231af.
2024-01-19 Migration to KiCad
2024-01-20 PCB preview correction
